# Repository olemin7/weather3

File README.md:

# platformio
source ~/.platformio/penv/bin/activate
pio run
pio project init --ide eclipse
# clock
clock with ntp synk
# Board
http://arduino.esp8266.com/stable/package_esp8266com_index.json
# lib 
https://github.com/olemin7/esp_libs

# referenses
schematic: https://circuits.io/circuits/3798057-net-clock-led
gtest
https://www.codeproject.com/Articles/811934/Cplusplus-unit-test-start-guide-how-to-set-up-Goog
https://github.com/google/googletest.git
arduino:
https://github.com/arduino/Arduino/blob/master/build/shared/manpage.adoc

# esp8266 reference
http://www.kloppenborg.net/blog/microcontrollers/2016/08/02/getting-started-with-the-esp8266

##wemos
Pin | Function    | ESP-8266 Pin | used
TX  | TXD         | TXD          |
RX  | RXD         | RXD          |
A0  | ADC, 3.3V   | A0           | battery
D0  | IO          | GPIO16       |
D1  | IO, SCL     | GPIO5        | 
D2  | IO, SDA     | GPIO4        | 
D3  | IO, 10k P-up| GPIO0        | 
D4  | IO, 10k P-up,LED|   GPIO2  | DHT.data
D5  | IO, SCK     | GPIO14       | 
D6  | IO, MISO    | GPIO12       | 
D7  | IO, MOSI    | GPIO13       | 
D8  | IO, 10k P-down, SS|  GPIO15|
G   | Ground      | GND          |
5V  | 5V          | -            |
3V3 | 3.3V        | 3.3V         |
RST | Reset       | RST          |

#ADC wemos
 A0--
    |
   220K
    |--- ADC
   100K
    |
   GND
 
#battery
 vbat 130k --A0
 adc val= 848,volt=3.72656 (3.95

#DHT
1 vcc (3.3V)
2 data (D4)
3 nc
4 GND (G)

#deepsleep
D0->RST Connect GPIO16 to RST pin only after uploading the code

https://github.com/adam-p/markdown-here/wiki/Markdown-Cheatsheet#lists
https://diyi0t.com/how-to-reduce-the-esp8266-power-consumption/
https://www.electronicshub.org/esp8266-deep-sleep-mode/

#usb not tetected ubuntu 22.04
https://stackoverflow.com/questions/70123431/why-would-ch341-uart-be-disconnected-from-ttyusb
sudo dmesg
...
 1553.747636] ch341 3-1.4:1.0: ch341-uart converter detected
[ 1553.748179] usb 3-1.4: ch341-uart converter now attached to ttyUSB0
[ 1554.300543] input: BRLTTY 6.4 Linux Screen Driver Keyboard as /devices/virtual/input/input38
[ 1554.302801] usb 3-1.4: usbfs: interface 0 claimed by ch341 while 'brltty' sets config #1
[ 1554.303356] ch341-uart ttyUSB0: ch341-uart converter now disconnected from ttyUSB0

sudo apt remove brltty

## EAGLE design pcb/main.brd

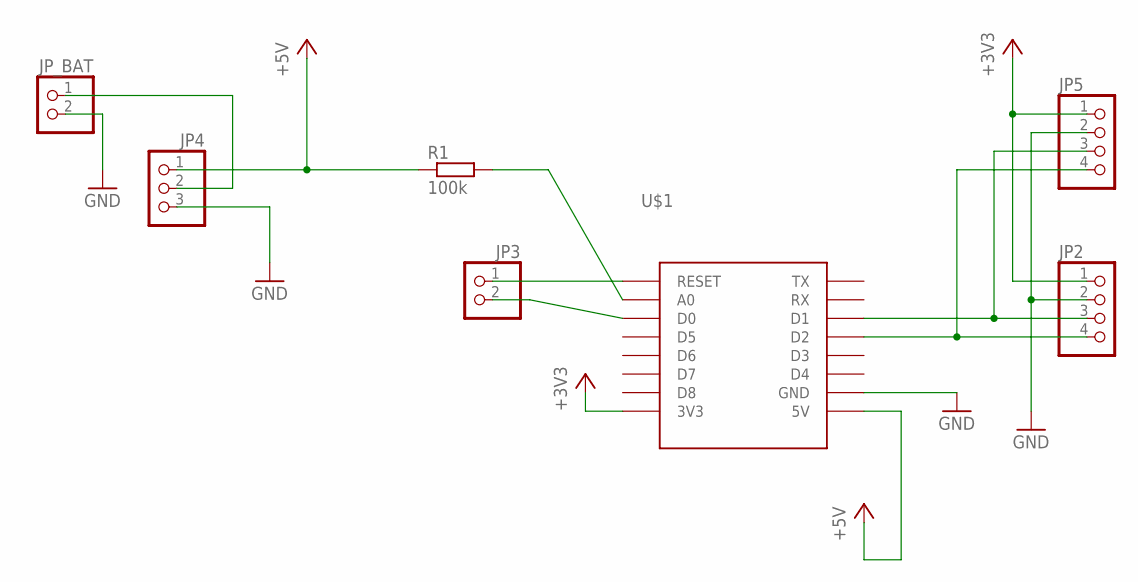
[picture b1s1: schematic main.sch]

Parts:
JP2, JP5: PINHD-1X4; 1X04
JP3: PINHD-1X2; 1X02
JP4: PINHD-1X3; 1X03
JP_BAT: PINHD-1X2; 1X02
R1: 100k; R0805
U$1: WEMOS-D1-MINI

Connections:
+3V3: JP2.1, JP5.1, U$1.3V3
+5V: JP4.1, R1.1, U$1.5V
GND: JP2.2, JP4.3, JP5.2, JP_BAT.2, U$1.GND
unnamed: JP4.2, JP_BAT.1
unnamed: R1.2, U$1.A0
unnamed: JP3.2, U$1.D0
unnamed: JP3.1, U$1.RESET
unnamed: JP2.4, JP5.4, U$1.D2
unnamed: JP2.3, JP5.3, U$1.D1

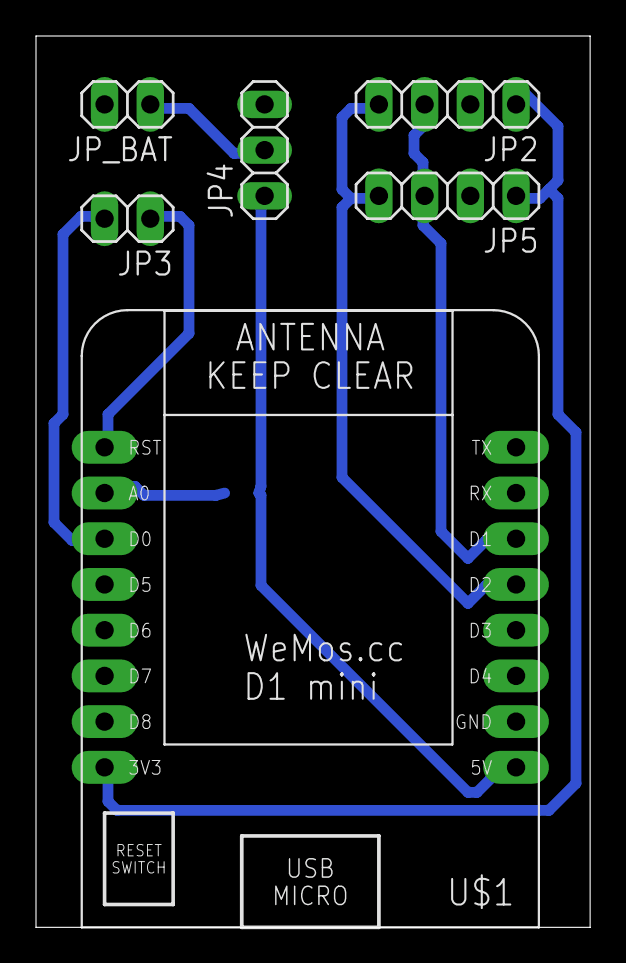
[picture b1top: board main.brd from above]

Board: 2 copper layers, 30.8 x 49.5 mm, 7 parts (1 on the bottom side), 9 nets.

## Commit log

2023-07-24 mqtt val to number
2023-09-02 refactoring
2023-11-09 +sht30
2025-02-22 upd schem
